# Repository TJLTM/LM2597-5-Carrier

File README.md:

# LM2597-Carrier
Hardware designs for the LM2597 5, 3.3 and Adjustable switching voltage regulators. 

basic design params that if you have something different then yous gots to readz the datasheet. 
1. input range 9-24 volts. 
2. 500mA max but will do about 300mA sustained indef 
3. the size, layout, connections are taylored to my projects so if you put in PR for some new connector type i might use it or probably not.

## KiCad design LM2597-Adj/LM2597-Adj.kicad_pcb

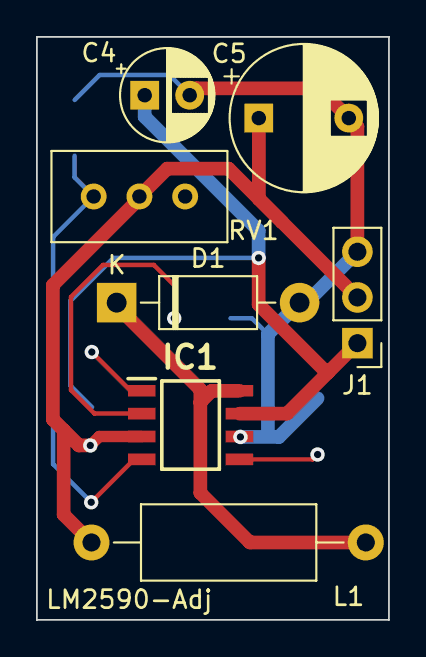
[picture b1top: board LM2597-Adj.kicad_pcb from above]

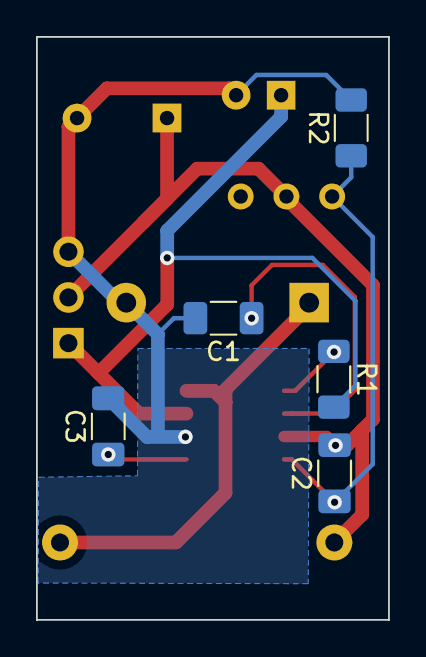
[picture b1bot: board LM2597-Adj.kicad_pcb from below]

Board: 2 copper layers, 19.6 x 32.4 mm, 12 parts (5 on the bottom side), 8 nets.

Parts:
C1, C2, C3: 0.1uF; C_1206_3216Metric_Pad1.33x1.80mm_HandSolder
C4: 68uF; CP_Radial_D5.0mm_P2.50mm
C5: 120uF; CP_Radial_D8.0mm_P5.00mm
D1: 1N5817; D_DO-41_SOD81_P10.16mm_Horizontal
IC1: LM2597MX-ADJ_NOPB; SOIC127P600X175-8N
J1: Conn_01x03; PinHeader_1x03_P2.54mm_Vertical
L1: 150mH; L_Axial_L9.5mm_D4.0mm_P15.24mm_Horizontal_Fastron_SMCC
R1: 4.7k; R_1206_3216Metric_Pad1.30x1.75mm_HandSolder
R2: 1k; R_1206_3216Metric_Pad1.30x1.75mm_HandSolder
RV1: 200k; Potentiometer_Bourns_3296W_Vertical

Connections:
+VDC: C4.1, IC1.7 (+VIN), J1.1, R1.2
GND: C1.2, C3.2, C4.2, C5.2, D1.2 (A), IC1.6 (GROUND), J1.3, R2.2
unnamed: D1.1 (K), IC1.8 (OUTPUT), L1.1
unnamed: C1.1, IC1.2 (DELAY)
unnamed: IC1.1 (ERROR_FLAG), R1.1
unnamed: C2.1, IC1.4 (FEEDBACK), R2.1, RV1.3
unnamed: C3.1, IC1.5 (~SHUTDOWN/SOFT-START)
VCC: C2.2, C5.1, IC1.3 (BIAS_SUPPLY), J1.2, L1.2, RV1.2

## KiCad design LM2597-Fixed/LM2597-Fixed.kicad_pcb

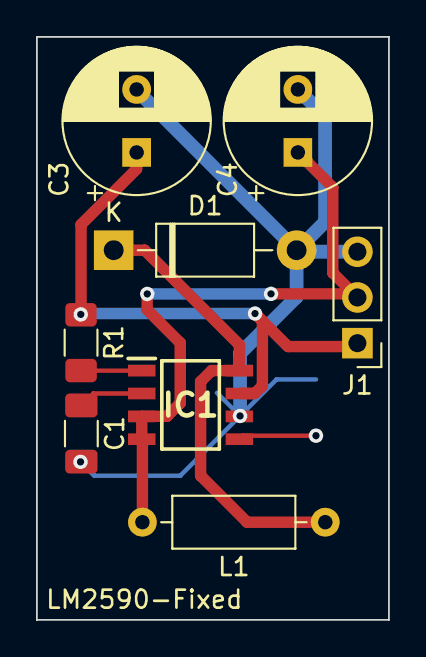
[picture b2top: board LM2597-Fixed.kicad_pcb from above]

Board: 2 copper layers, 19.6 x 32.4 mm, 9 parts (1 on the bottom side), 7 nets.

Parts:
C1, C2: 0.1uF; C_1206_3216Metric_Pad1.33x1.80mm_HandSolder
C3: 68uF; CP_Radial_D8.0mm_P3.50mm
C4: 120uF; CP_Radial_D8.0mm_P3.50mm
D1: 1N5817; D_DO-41_SOD81_P10.16mm_Horizontal
IC1: LM2597MX-5.0_NOPB; SOIC127P600X175-8N
J1: Conn_01x03; PinHeader_1x03_P2.54mm_Vertical
L1: 150uH; L_Axial_L6.6mm_D2.7mm_P10.16mm_Horizontal_Vishay_IM-2
R1: 10k; R_1206_3216Metric_Pad1.30x1.75mm_HandSolder

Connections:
+VDC: C3.1, IC1.7 (+VIN), J1.1, R1.1
GND: C1.2, C2.2, C3.2, C4.2, D1.2 (A), IC1.6 (GROUND), J1.3
unnamed: D1.1 (K), IC1.8 (OUTPUT), L1.1
unnamed: C1.1, IC1.2 (DELAY)
unnamed: IC1.1 (ERROR_FLAG), R1.2
unnamed: C2.1, IC1.5 (~SHUTDOWN/SOFT-START)
VCC: C4.1, IC1.3 (BIAS_SUPPLY), IC1.4 (FEEDBACK), J1.2, L1.2

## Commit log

2022-04-20 initial blank projects for 5v and 3.3v chips
2022-04-20 just need to do the 3.3 board layout. will do that once ihave the 5v done so i can make the base carrier the same size and mounting.
2022-04-20 adding the Adj project.
2022-04-20 copy pasta from other designs and need to get the layouts done and synced.
2023-05-04 updating the 5v to kicad 7 and removing the 3.3
2023-05-04 rename to fixed
2023-05-04 rename to fixed.
2023-05-05 routed and drc'ed
2023-05-05 Prepping for Fab.
    Added Fab Files for Both and included the Zip from the PCBway plugin
    Added ibom for both
    Added Datasheet for LM2597
2024-11-20 updated all of these to SMD parts
